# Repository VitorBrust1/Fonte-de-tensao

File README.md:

# Projeto Fonte de Tensão
  Projeto da disciplina Elêtronica para Computação (SSC0180-2020101) 2020, USP São Carlos.
O projeto consiste no desenvolvimento e simulação de uma fonte de tensão que converta a corrente alternada da tomada de tensão 110V ou de 220V  para uma tensão ajustável de 3V a 12V de corrente contínua com capacidade de 100mA.

# Simulação da fonte no Falstad

- ## Diagrama

 - ## Componentes utilizados
 
 	- Capacitor: Estabilização da tensão no circuito por meio do armazenamento de quantidades de energia.
	
	- Ponte de Diodos: Aproveitar os dois ciclos da tensão (Ajuda na transformação da corrente alternada vinda da tomada em corrente contínua no circuito).
	
	- Diodo Zener: Limitar a tensão que passa pelo circuito, estabelecendo uma tensão limite.
	
	- Potênciometro: Resistor em que é possível ajustar sua resistência.
	
	- Resistor: Limitar a corrente elétrica em um circuito.
	
	- Switch: Permitir a passagem de corrente elétrica para o circuito, funcionando como uma chave de liga e desliga.
	
	- Transistor NPN: Regula a corrente de coletor a partir da corrente de base, na qual a corrente de coletor é 100x a corrente de base.
	
	- Transformador: Converter a Tensão de 110V ou de 220V da tomada para 20V no circuito.
	
 - ## Preços e especificações
 
| Nome | Especificações | Preço(unidade) | Quantidade |
|--|--|--|--|
| Capacitor | 470µF / 25V | [0.33 R$](https://www.baudaeletronica.com.br/capacitor-eletrolitico-470uf-25v.html) | 1 |
| Ponte de Diodo 2W10 | 1000V / 2A | [0.90 R$](https://produto.mercadolivre.com.br/MLB-1425220046-20pcs-diodo-2w10-2a-1000v-ponte-retificadora-queima-de-estoq-_JM?quantity=1#position=2&type=item&tracking_id=7da9028e-051c-4f32-9131-fbebcf4951f3) | 1 |
| Diodo Zener | 13V / 0.1A | [1.06 R$](https://produto.mercadolivre.com.br/MLB-911630639-10-pcs-diodo-zener-13v-1w-1n4743frete-brasil-r1200-_JM?quantity=1#position=1&type=item&tracking_id=04c09c17-2e4c-4791-8f42-f5dba14f20db) | 1 |
| Potênciometro | 1KΩ / 0.2W | [1.23 R$](https://www.baudaeletronica.com.br/potenciometro-linear-rotativo-de-1k-1000.html) | 1 |
| Resistor | 390Ω / 0.25W | [0.12 R$](https://produto.mercadolivre.com.br/MLB-873476711-resistor-390-ohms-14w-5-kit-100-pcs-_JM?quantity=1#position=21&type=item&tracking_id=bb601283-825f-405d-88d3-7b98e6115a90) | 1 |
| Resistor | 470Ω / 0.25W | [0.86 R$](https://produto.mercadolivre.com.br/MLB-868726201-kit-10-x-resistor-470-ohm-5-14w-025w-leds-5mm-arduino-pic-_JM?quantity=1#position=3&type=item&tracking_id=47bb88f9-93a7-404e-95fa-2983eb8989df) | 1 |
| Switch | 250V / 6A | [8.90 R$](https://produto.mercadolivre.com.br/MLB-1273705844-chave-gangorra-redonda-on-off-spst-_JM?quantity=1#position=17&type=item&tracking_id=b7cc1b9b-29d5-4e13-a0b3-b4ef4f160cbb) | 1 |
| Transistor NPN 2n2222a| 60V / 0.8A | [0.60 R$](https://produto.mercadolivre.com.br/MLB-1222136291-20-pecas-transistor-npn-2n2222a-_JM?quantity=1#position=1&type=item&tracking_id=a8cdd5b8-c51f-44e9-a07f-8d04e5635adc) | 1 |	
| Transformador | (110V / 220V) / 1.2A / 12V + 12V | [35.00 R$](https://produto.mercadolivre.com.br/MLB-791922427-transformador-1212-12a-trafo-1200ma-12v-12v-ac-12a-trafo-_JM?quantity=1) | 1 |

**Custo Total**: 49.00 R$.

 - ## Justificativa para escolha dos componentes

	- Transformador: Suporta uma corrente de 1.2A, e a corrente mínima que deve suportar no circuito é de aproximadamente 420mA.
	
	- Ponte de Diodos 2W10: Aguenta uma tensão de até 1000 V e bloqueia uma corrente de até 2 Amperes.
	
	- Capacitor de 470µF: Aguenta uma tensão de até 25V, sendo que a tensão máxima nessa parte do circuito é de aproximadamente 21V.
	
	- Resistor de 470Ω: Limita a corrente que passa pelo diodo zener. Aguenta uma potência de até 0.25W, sendo o mínimo necessário de aproximadamente 0.13W.
	
	- Resistor de 390Ω: Limitar a tensão da saída em no mínimo 3V, podendo assim colocar o potênciometro em resitência máxima. Aguenta uma potência de 0.25W, sendo o mínimo necessário aproximadamente 0.12W.
	
	- Diodo Zener 13V: Limita a tensão em 13V. Dessa forma, como ao passar pelo transistor há uma perda de 0.7V a saída terá uma tensão de no máximo 12.3V. Assim, para a saída ter exatos 12V, o potênciometro não necessita ser colocado em sua mínima resistência.
	
	- Transistor NPN: Aguenta 60V de tensão e suporta 800mA de corrente, sendo que a corrente máxima que passará por ele é de 100mA.
	
	- Potênciometro de 1KΩ: Suporta uma potência de 0.20W, e no circuito tem que suportar 0.13W. Regula a corrente que vai para a base do transistor NPN, permitindo que na saída tenha uma variação de 3V ~ 12V e 24.5mA ~ 100mA.
  
- ## Link para o circuito no falstad
  http://tinyurl.com/yboz8xpa
- ## Link para o vídeo explicativo:
  https://www.youtube.com/watch?v=hgTtiHER5eE&feature=youtu.be
# Projeto do Esquemático e do PCB no EAGLE

- ## Esquemático

- ## PCB

# Modificações do circuito após reunião com o professor
  O professor Eduardo Simões recomendou aumentar a resistência dos resistores e do potênciometro para diminuir o desperdício de corrente, a qual passa pelo diodo zener e pelo potênciometro. Após os ajustes foram verificadas as seguintes alterações:
  
  	- Resistor: 390Ω -> 2.2kΩ.
	- Resistor: 470Ω -> 1kΩ.
	- Potênciometro: 1kΩ -> 5kΩ.
	
 Por meio dessas alterações haverá menos desperdício de corrente no circuito e os valores de saída da fonte não sofrerão desvios consideráveis ou que comprometam o objetivo do trabalho. Junto a isso, o preço dos novos componentes se assemelham com o preço dos componentes do projeto original e, portanto, o projeto, após as moficações, não sofrerá aumento no custo de produção.
 
 - ## Link para o circuito no falstad após modificações recomendadas
 
 	http://tinyurl.com/y8upkvnn
	
 - ## Diagrama após modificações recomendadas

 - ## Preços e especificações após modificações recomendadas
 
 | Nome | Especificações | Preço(unidade) | Quantidade |
|--|--|--|--|
| Resistor | 2.2kΩ / 0.25W | [0.08 R$](https://www.baudaeletronica.com.br/resistor-2k2-5-1-4w.html) | 1 |
| Resistor| 1kΩ / 0.25W | [0.08 R$](https://www.baudaeletronica.com.br/resistor-1k-5-1-4w.html)| 1 |
| Potênciometro | 5kΩ / 0.20W | [1.09 R$](https://www.baudaeletronica.com.br/potenciometro-linear-de-5k-5000.html)| 1 |

**Preço Total após modificações**: 48.04 R$.

# Participantes

 - João Antônio Misson Milhorim. Número USP: 18834331.
 - João Victor Sene Araújo. Número USP: 11796382.
 - Vitor Caetano Brustolin. Número USP: 11795589. Github: https://github.com/VitorBrust1

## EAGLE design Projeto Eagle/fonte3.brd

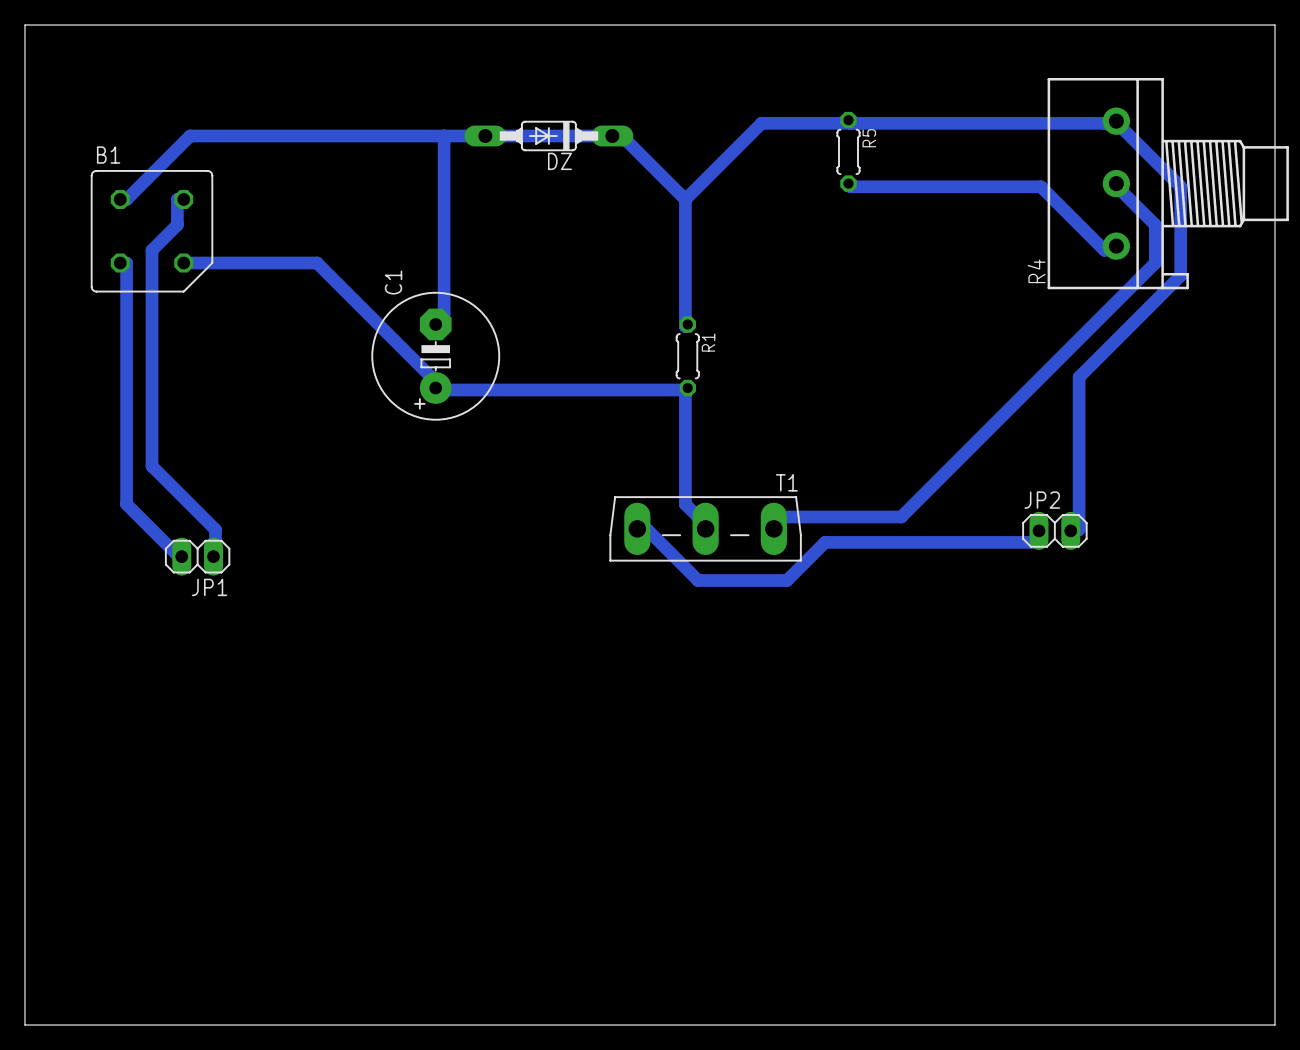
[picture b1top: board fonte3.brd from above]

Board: 2 copper layers, 100.0 x 80.0 mm, 9 parts (0 on the bottom side), 7 nets.

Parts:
B1: 1KAB
C1: 470µF; E5-10,5
DZ: 13V; SOD81
JP1, JP2: 1X02
R1: 470Ω; 0204/5
R4: 3RP/1610N
R5: 390Ω; 0204/5
T1: SOT93V

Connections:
unnamed: B1.AC1, JP1.2
unnamed: B1.AC2, JP1.1
unnamed: B1.+, C1.+, R1.2, T1.C
unnamed: R4.1, R5.2
unnamed: R4.2, T1.B
unnamed: JP2.1, T1.E
unnamed: B1.-, C1.-, DZ.A, DZ.C, JP2.2, R1.1, R4.3, R5.1

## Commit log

2020-06-29 Create Fonte Eagle
